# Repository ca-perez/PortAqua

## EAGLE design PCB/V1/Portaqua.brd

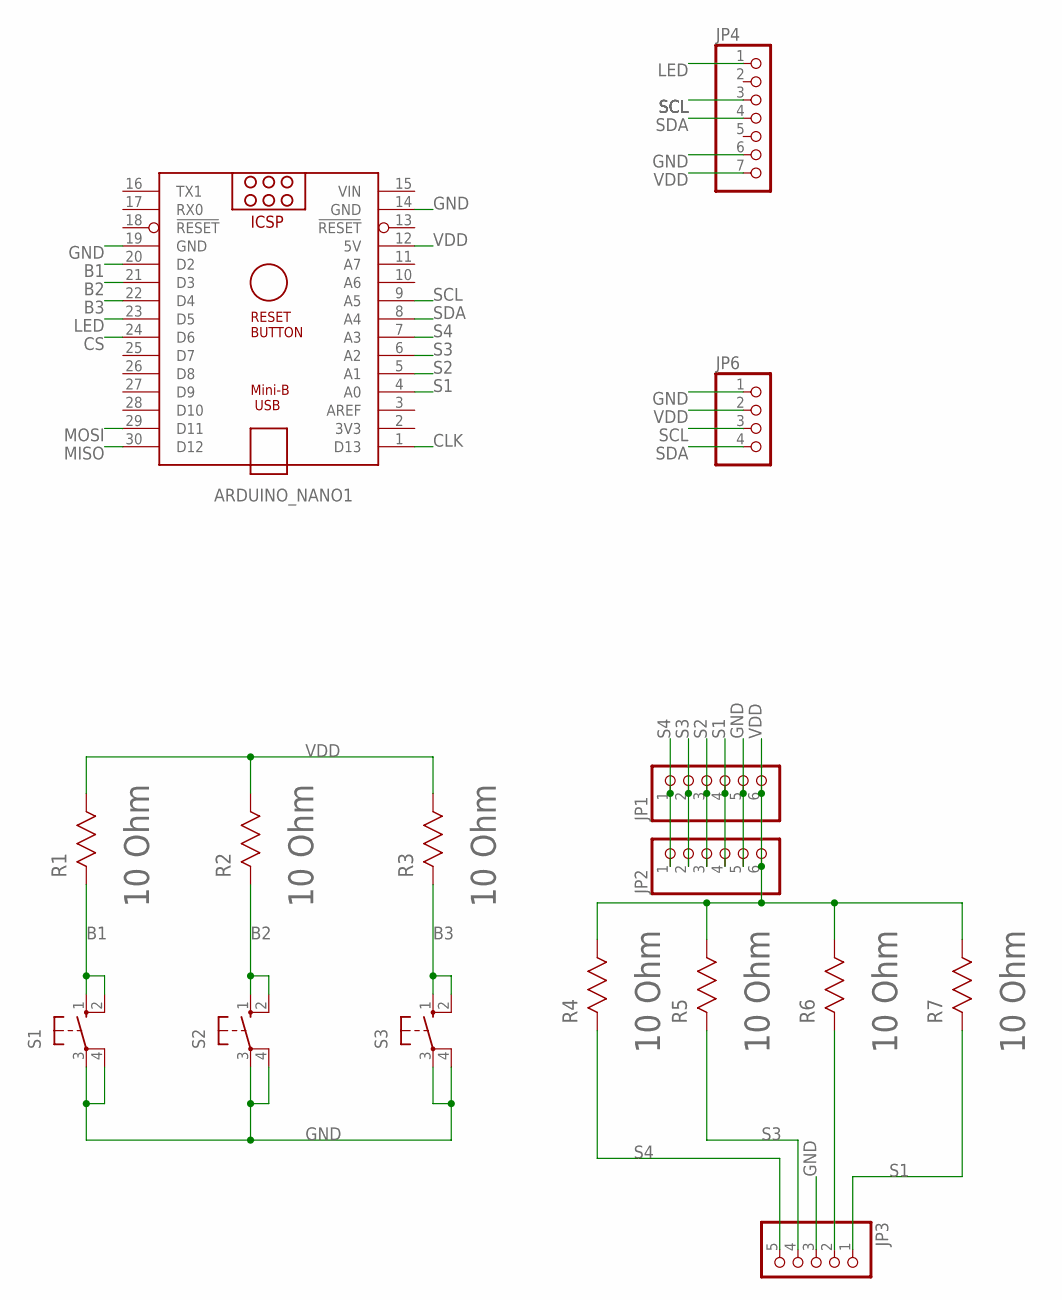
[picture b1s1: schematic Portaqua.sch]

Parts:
ARDUINO_NANO1: ARDUINO_NANO
JP1, JP2: PINHD-1X6; 1X06
JP3: PINHD-1X05_2.54-SMD-90°; 1X05SMD/90
JP4: PINHD-1X7; 1X07
JP6: PINHD-1X4; 1X04
R1, R2, R3, R4, R5, R6, R7: 10 Ohm; RESC3216X71N
S1, S2, S3: 10-XX; B3F-10XX

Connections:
B1: ARDUINO_NANO1.20 (D2), R1.2 (R2), S1.1 (S), S1.2 (S1)
B2: ARDUINO_NANO1.21 (D3), R2.2 (R2), S2.1 (S), S2.2 (S1)
B3: ARDUINO_NANO1.22 (D4), R3.2 (R2), S3.1 (S), S3.2 (S1)
CLK: ARDUINO_NANO1.1 (D13)
CS: ARDUINO_NANO1.24 (D6)
GND: ARDUINO_NANO1.14 (GND), ARDUINO_NANO1.19 (GND), JP1.5, JP2.5, JP3.3, JP4.6, JP6.1, S1.3, S1.4 (P1), S2.3, S2.4 (P1), S3.3, S3.4 (P1)
LED: ARDUINO_NANO1.23 (D5), JP4.1
MISO: ARDUINO_NANO1.30 (D12)
MOSI: ARDUINO_NANO1.29 (D11)
unnamed: JP3.2, R6.2 (R2)
S1: ARDUINO_NANO1.4 (A0), JP1.4, JP2.4, JP3.1, R7.2 (R2)
S2: ARDUINO_NANO1.5 (A1), JP1.3, JP2.3
S3: ARDUINO_NANO1.6 (A2), JP1.2, JP2.2, JP3.4, R5.2 (R2)
S4: ARDUINO_NANO1.7 (A3), JP1.1, JP2.1, JP3.5, R4.2 (R2)
SCL: ARDUINO_NANO1.9 (A5), JP4.3, JP6.3
SDA: ARDUINO_NANO1.8 (A4), JP4.4, JP6.4
VDD: ARDUINO_NANO1.12 (5V), JP1.6, JP2.6, JP4.7, JP6.2, R1.1 (R1), R2.1 (R1), R3.1 (R1), R4.1 (R1), R5.1 (R1), R6.1 (R1), R7.1 (R1)
VIN: ARDUINO_NANO1.15 (VIN)

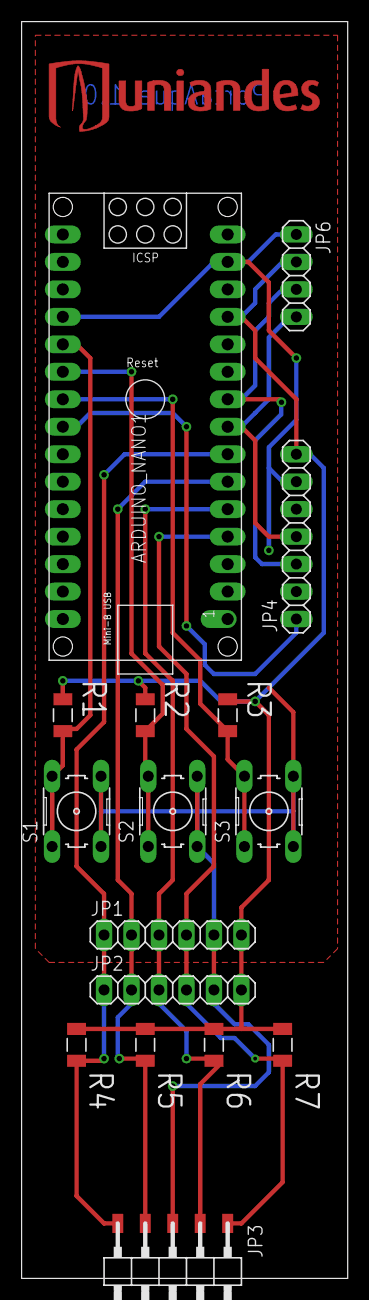
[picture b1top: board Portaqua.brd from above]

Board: 2 copper layers, 30.1 x 116.2 mm, 17 parts (0 on the bottom side), 13 nets.

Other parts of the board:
U$1: UNIANDES25MM

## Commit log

2021-12-14 Create V1
